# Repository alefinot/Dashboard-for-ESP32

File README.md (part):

# Dashboard++ for ESP32

**Dashboard++** is an ultra-high-performance, production-grade automotive digital instrument cluster and telemetry solution designed for motorcycles, cars, and custom electric/combustion vehicles powered by the **ESP32 WROOM-32** dual-core microcontroller.

Featuring a 4.0-inch ILI9488 TFT display (480×320 resolution) driven over a 60 MHz SPI bus using **LovyanGFX** with PROGMEM-mapped VLW fonts, Dashboard++ blends real-time multi-sensor fusion algorithms, sprite-based anti-aliased digit rendering, dirty-rendering optimizations, hysteresis-based dynamic CPU frequency scaling, persistent NVS configuration management, an Open-Meteo live weather widget, and a complete single-page Web application served over WiFi with REST API control, NVS backup/restore, and firmware updates pushed to it over the LAN.

---

## Technical Table of Contents
1. [Executive Overview](#executive-overview)
2. [System Architecture & Task Allocation](#system-architecture--task-allocation)
3. [Hardware Component Specifications](#hardware-component-specifications)
4. [Hardware Pinout Matrix](#hardware-pinout-matrix)
5. [Software Architecture & Mathematical Models](#software-architecture--mathematical-models)
   - [Dual-Source Speed Fusion & Odometer Engine](#1-dual-source-speed-fusion--odometer-engine)
   - [Anti-Aliased GFX Engine & 7-Segment Fonts](#2-anti-aliased-gfx-engine--7-segment-fonts)
   - [Piecewise Linear Fuel Calibration & Filtering](#3-piecewise-linear-fuel-calibration--filtering)
   - [Steinhart-Hart Coolant Temperature Math](#4-steinhart-hart-coolant-temperature-math)
   - [Fuel Economy & Performance Drag Timer](#5-fuel-economy--performance-drag-timer)
   - [Power Management & Dynamic CPU Scaling](#6-power-management--dynamic-cpu-scaling)
6. [Embedded Web UI & REST API Reference](#embedded-web-ui--rest-api-reference)
7. [NVS Configuration Parameter Reference](#nvs-configuration-parameter-reference)
8. [Android Companion App](#android-companion-app)
   - [The shell: one bar, one pager, one list](#the-shell-one-bar-one-pager-one-list)
   - [The garage: a card is a vehicle and the unit that belongs to it](#the-garage-a-card-is-a-vehicle-and-the-unit-that-belongs-to-it)
   - [Identity: which dashboard belongs to which card](#identity-which-dashboard-belongs-to-which-card)
   - [Connection: where connecting happens, and where it does not](#connection-where-connecting-happens-and-where-it-does-not)
   - [Trip log: one file per power session, tagged with the card](#trip-log-one-file-per-power-session-tagged-with-the-card)
   - [Photos: pick, crop, one JPEG per vehicle](#photos-pick-crop-one-jpeg-per-vehicle)
   - [Building and testing the app](#building-and-testing-the-app)
9. [Codebase Architecture & File Map](#codebase-architecture--file-map)
10. [Build, Installation & Flashing Guide](#build-installation--flashing-guide)
11. [Simulation & Demo Mode](#simulation--demo-mode)
12. [License & Credits](#license--credits)

---

## Executive Overview

Dashboard++ replaces legacy analog or basic digital gauges with an automotive-grade telemetry console. Key capabilities include:

- **Dual Speed Fusion (Hall Effect + GNSS):** Dynamically fuses microsecond-level hardware interrupt pulses with NMEA GPS speed vectors, adjusting confidence based on satellite lock quality ($N_{\text{sat}}$) and cross-checking delta errors.
- **Sprite-Based Anti-Aliased Speed Rendering:** The main speed readout is pre-rendered to an off-screen LGFX_Sprite using a 120px VLW 7-segment digital font, then pushed to the display in a single DMA transfer — reducing SPI bus contention and eliminating per-digit draw calls.
- **PROGMEM VLW Font System:** All fonts (Conthrax SemiBold and DS-DIGIT variants) are compiled into flash as PROGMEM byte arrays (generated from the `.vlw` sources in `data/Fonts/` by `scripts/vlw_to_header.py`), loaded at build time via `loadVLWFont()` — zero DRAM per glyph, no runtime filesystem lookups.
- **Dirty-Rendering Frame Pipeline:** Element state tracking ensures only mutated visual regions are drawn to the SPI bus, with dedicated per-element refresh rate throttles for speed, satellite count, timer, battery, fuel economy, and average speed.
- **Configurable 7-Segment Digital Fonts:** 120px (sprite) and 28px (direct) seven-segment fonts with background "ghost digit" rendering (888 backdrop effect) and fully user-configurable integer and decimal digit boundaries for all telemetry counters.
- **Full Sensor Suite Integration:** Precise fuel level monitoring (20-point piecewise linear calibration table + EMA filtering), engine coolant thermistor telemetry (Steinhart-Hart equation), battery voltage divider monitoring, trip fuel economy tracking, **trip average speed**, and a **session max speed (Vmax)** readout display.
- **FreeRTOS Dual-Core Multitasking:** Strict core isolation — the continuous ~1.1KB/s GNSS UART stream is quarantined in its own Core 0 task (bulk ring-buffer read, bounded per tick, sitting below the WiFi stack), while the vehicle sensor suite and UI rendering run on Core 1, so a GPS stream backlog can never stall the dashboard or freeze any real-time value.
- **Embedded Web Management Portal:** Embedded single-page Web application accessible over SoftAP or local WiFi network featuring grouped card-based configuration UI with live search, real-time performance telemetry panel (FPS, CPU frequency/temp, RAM, flash storage), interactive sliders, color pickers, NVS backup/restore, web serial terminal stream, and OTA firmware updating by uploading a firmware file (from the Web UI file picker, or from the Android app, which is the intended path).
- **Hysteresis-Based Dynamic CPU Scaling:** Three-state frequency governor (240/160/80 MHz) with hysteresis deadbands prevents oscillation, and thermal throttling automatically caps frequency at configurable warning/critical temperature thresholds.

---

## System Architecture & Task Allocation

The system leverages the ESP32's Xtensa dual-core processor via FreeRTOS tasks to guarantee deterministic sensor sampling without visual stuttering or UI delays.

```
┌─────────────────────────────────────────────────────────────────────────────────┐
│                            ESP32 WROOM-32 DUAL-CORE                             │
├────────────────────────────────────────┼────────────────────────────────────────┤
│    CORE 0  (GNSS Stream & Network)     │  CORE 1  (Vehicle Sensors & Display)   │
├────────────────────────────────────────┼────────────────────────────────────────┤
│┌──────────────────────────────────────┐│┌──────────────────────────────────────┐│
││ Task: GpsTaskCore0 (Prio 2, 10KB)    │││ Task: SensorTaskCore1 (Prio 2, 10KB) ││
││                                      │││                                      ││
││• UART2 @ 115200 bulk ring drain      │││• Hall Sensor GPIO33 ISR              ││
││  (readBytes() batch, 1024 B/tick cap)│││• ADC: Fuel (32), Temp (36), Bat (35) ││
││• TinyGPS++ NMEA + UBX NAV-PVT parse  │││• Fuel Economy & Accel Timer          ││
││• Speed Fusion & Odometer calc        │││• Trip Average Speed                  ││
││• GNSS Epoch Time Sync -> settimeofday│││• Safe Thread Sync via g_stateMutex   ││
││• Safe Thread Sync via g_stateMutex   │││                                      ││
││                                      │││• Safe Thread Sync via g_stateMutex   ││
││──────────────────────────────────────│││──────────────────────────────────────││
││ Task: WebTaskCore0 (Prio 1, 12KB)    │││ Main Loop (Priority 1)               ││
││                                      │││                                      ││
││• SoftAP (Dashboard_Config) & STA     │││• Dirty-Rendering Frame Pipeline      ││
││• WebServer HTTP Handlers             │││• LovyanGFX SPI Driver (60 MHz)       ││
││• ArduinoOTA Firmware Listener        │││• Sprite-Based Speed (120px VLW)      ││
││• Serial Log Streaming API            │││• Hysteresis CPU Scaling (80/160/240) ││
│└──────────────────────────────────────┘││• Auto Night-Mode Backlight PWM       ││
│                                        ││• Ignition Deep Sleep State Machine   ││
│                                        ││• Telemetry Logging to 4KB Ring       ││
│                                        │└──────────────────────────────────────┘│
└─────────────────────────────────────────────────────────────────────────────────┘
```

> [!NOTE]
> The GNSS task sits on Core 0 **below** the WiFi/HTTPD/LWIP stack on purpose: the module streams
> ~1.1KB/s continuously and the drain is I/O-gated at the byte arrival rate, so it can never
> out-run the stream. GPS is 1Hz-tolerant data, so if the network preempts the drain, only GPS
> values lag — the vehicle sensors and the screen are never touched.

> [!NOTE]
> The **weather fetch task** (Core 0, spawned by `startWeatherFetch()` on Core 1) polls the Open-Meteo
> API on a configurable interval (`WEATHER_REFRESH_MIN`) and stores the result in a dedicated
> `g_weatherData` struct. A 30 s guard asks a stuck fetch to abort (the fetch polls
> `weatherAbort` at its checkpoints and HTTP calls carry 8 s connect/read timeouts) so it unwinds
> and deletes itself rather than being killed with `vTaskDelete()`; while an aborted fetch is still
> alive, `startWeatherFetch()` refuses to stack a second one. A config save triggers an
> instant refetch with a 2 s retry backoff.

> [!NOTE]
> Every FreeRTOS task is started through `startTask()` in `src/main.cpp`, which checks the
> `xTaskCreatePinnedToCore()` return value, retries once on half the requested stack (a reduced
> stack usually fits and beats a missing subsystem) and, if that fails too, records the task in a
> `failedTasksMask` and logs it with the free heap. A task that cannot start is therefore named in
> the boot log instead of silently missing — the failure that used to show up only as a frozen
> heartbeat, no Web UI or dead sensors.

---

## Hardware Component Specifications

| Component | Part / Model | Protocol / Signal | Specifications |
| :--- | :--- | :--- | :--- |
| **Microcontroller** | ESP32-WROOM-32 | Xtensa 32-bit LX6 | Dual-core 240 MHz, 520 KB SRAM, 4 MB SPI Flash, RTC IO |
| **Display Panel** | ILI9488 TFT LCD (4.0") | SPI3 (16-bit RGB565) — SCLK GPIO18, MOSI GPIO23, CS GPIO5, DC GPIO27, RST GPIO14 (no MISO) | 480×320 pixels, 60 MHz SPI bus speed (clamped to 1–80 MHz), hardware CS/DC/RST |
| **Display Backlight** | LED Backlight (`BL_DISPLAY`, GPIO12) | LEDC PWM — pin-based `ledcAttach(BL_DISPLAY, BL_PWM_HZ, 8)` | hardware PWM at `BL_PWM_HZ` (default **12 kHz** — above the audible range — configurable 1–40 kHz), 8-bit resolution (256 brightness levels), logarithmic fading; the LEDC channel is assigned by the arduino-esp32 3.x wrapper |
| **GNSS Module** | BZGNSS P25 Pro (u-blox M10) | UART2 (RX=GPIO16, TX=GPIO17) | 115200 baud (configurable), UBX NAV-PVT / NMEA 0183 stream (module is preconfigured — the firmware is receive-only), 10 Hz update rate, multi-constellation (GPS/GLONASS/BDS/Galileo), UTC epoch time synchronization |
| **Wheel Speed Sensor** | Hall Effect Interrupt | GPIO33 (Input Pullup) | Any-edge ISR stamps the edges; interval/filter logic runs on the sensor task, microsecond timing |
| **Fuel Level Sensor** | Marine Resistive Sender (capacitive touch removed in v1.3.6) | GPIO32 (ADC1_CH4) | Voltage divider behind an excitation resistor, ohm-domain calibration table (up to 20 points), oversampling + EMA smoothing, open/short detection |
| **Engine Temp Sensor** | NTC Thermistor (10k/100k) | GPIO36 (ADC1_CH0) | Analog 0–3.3V, Steinhart-Hart equation, voltage divider balance |
| **Battery Voltage** | Voltage Divider (5.7:1) | GPIO35 (ADC1_CH7) | Analog 0–3.3V, range 0–18.8V DC, sampled every 500 ms |
| **Power / Ignition** | Ignition Key Sense Line | GPIO4 | High=Ignition ON, Low=Power Lost → Animated Deep Sleep |

---

## Hardware Pinout Matrix

> For the board side of the same information — which connector/plug each signal lives on,
> with the connector pin numbers and the small-part roles — see
> [`hardware/PINOUT.md`](hardware/PINOUT.md).

| ESP32 Pin | Function Name | Peripheral Type | Signal Direction | Hardware Configuration & Notes |
| :---: | :--- | :--- | :---: | :--- |
| **GPIO0** | BOOT | Factory Reset | Input (Pullup) | `pinMode(0, INPUT_PULLUP)`; **hold BOOT 4 s, release, hold 4 s again** within the first 30 s after boot to wipe the config — the reliable path. The release in the middle is required because GPIO0 is shared with the serial adapter's DTR line through the auto-reset transistor: a PC that holds DTR asserted keeps GPIO0 low forever, and the old single 8 s hold wiped the config on every boot with nobody touching the board. The serial fallback (send `RESET` within the first 2 s of boot) is matched against a rolling 32-character window, so boot-log echo can no longer fill the capture and hide the command (issue #39) |
| **GPIO1** | Console TX | Debug Console | Output | `Serial.setPins(1, 3)` pins the console explicitly (arduino-esp32 3.x moved the UART1 default to GPIO26/27) |
| **GPIO3** | Console RX | Debug Console | Input | Same `Serial.setPins(1, 3)` call |
| **GPIO4** | `POWER_SENSE_PIN` | Power Sense | Input (No Pull) | Ignition sense line; triggers EXT0 RTC wake up from deep sleep |
| **GPIO5** | `CS_DISPLAY` | SPI Chip Select | Output | Hardware SPI CS for ILI9488 Display |
| **GPIO12** | `BL_DISPLAY` | Backlight PWM | Output | Pin-based `ledcAttach(BL_DISPLAY, BL_PWM_HZ, 8)` — frequency is the `BL_PWM_HZ` knob (default 12 kHz, above hearing), 8-bit resolution |
| **GPIO14** | `SPI_RST` | Display Reset | Output | Active-Low hardware reset line for ILI9488 |
| **GPIO16** | `GNSS_UART2_RX_PIN` | GPS Serial RX (UART2) | Input | Connected to the GNSS module TX pin. Receive-only: the firmware never transmits to the module |
| **GPIO17** | `GNSS_UART2_TX_PIN` | GPS Serial TX (UART2) | Output | Connected to the GNSS module RX pin; configured but idle - no UBX command is ever sent |
| **GPIO18** | `cfg.pin_sclk` | SPI Clock | Output | Hardcoded in `gfx.cpp` (SPI3_HOST), 60 MHz default |
| **GPIO23** | `cfg.pin_mosi` | SPI Master Out | Output | Hardcoded in `gfx.cpp`, LCD data/command stream |
| **GPIO25** | `TRIP_RESET_PIN` | Trip Reset Button | Input (Pullup) | Momentary push button to GND; hold `TRIP_RESET_HOLD_MS` to zero the trip stats (issue #17). Internal ~45 kΩ pull-up, no external parts |
| **GPIO27** | `SPI_DC` | Data / Command | Output | High = Data, Low = Command for ILI9488 controller |
| **GPIO32** | `FUEL_TOUCH_PIN` | Fuel sender input | Input | Dedicated ADC1 Channel 4 pin: 3V3 → `FUEL_EXC_RES_OHM` → GPIO32 → sender → tank ground (capacitive touch removed in v1.3.6) |
| **GPIO33** | `HALL_SENSOR_PIN` | Hall Interrupt | Input (Pullup) | Any-edge (`CHANGE`) hardware interrupt: the ISR timestamps both transitions, the filter chain validates them on the sensor task |
| **GPIO34** | `LIGHT_SENSOR_PIN` | Ambient Light | Input (No Pull) | LDR ambient light sensor for auto-brightness (calibrated via `/api/ambient/cal-dark` / `cal-bright`) |
| **GPIO35** | `BATTERY_SENSE_PIN` | Battery ADC | Input (No Pull) | Connected to 5.7:1 precision resistor divider node |
| **GPIO36** | `TEMP_SENSE_PIN` | Engine Temp ADC | Input (No Pull) | Connected to NTC thermistor / balance resistor divider node |

> [!IMPORTANT]
> GPIO32 is dedicated to the fuel ADC input to avoid pin-sharing conflicts with the GPIO33 Hall interrupt hardware line.

> [!NOTE]
> This matrix matches the code (`src/dashboard.h` pin defines and the hardcoded display SPI pins in `src/gfx.cpp`), which is the source of truth. The GNSS serial pair moved from GPIO25/26 to **GPIO16/17** during the pin-swap test and stayed there, which is what freed **GPIO25** for the trip-reset button; **GPIO26** stays free as the spare for a second button. Strapping pins (`GPIO0`, `GPIO2`, `GPIO5` = `CS_DISPLAY`, MTDI/`GPIO12`, MTDO/`GPIO15`) are deliberately not used for buttons — a button to GND can hold them the wrong way during reset and block boot. The display SPI bus has no MISO line (`cfg.pin_miso = -1`), and GPIO21/22 (former compass I²C) are unused.

---

## Software Architecture & Mathematical Models

### 1. Dual-Source Speed Fusion & Odometer Engine

Dashboard++ features a dual-source speed calculation engine that combines low-latency wheel rotation timing with absolute satellite GPS telemetry.

#### Hall Sensor Calculation & 5-Layer Defense Pipeline
Speed is derived from microsecond timing between consecutive interrupt pulses on GPIO33, protected by an end-to-end 5-layer defense pipeline that eliminates spark ignition EMI glitches, prevents baseline collapse during deceleration, and bounds rate-of-change to physical limits:

1. **Layer 1: Measured Pulse-Width Qualification (Glitch Filter):** Real wheel magnets hold GPIO33 LOW for hundreds of microseconds (one revolution at 200 km/h is still 29.7 ms long). High-frequency ignition coil ringing collapses back to HIGH within <10 µs. The GPIO ISR used to prove the width by busy-waiting `HALL_PULSE_MIN_US` and re-sampling `REG_READ(GPIO_IN1_REG)` **inside** the interrupt, which masked interrupts on that core for up to 1 ms per glitch (~86 bytes of GNSS RX at 115200 baud). Now the interrupt is `CHANGE` (both edges), the ISR only stamps the transition time into a 64-slot ring, and the qualification is *measured*: `rise − fall ≥ HALL_PULSE_MIN_US` (default 150 µs, WebUI-tunable, clamped to 10…1000 µs). A glitch is dropped before any interval logic runs, exactly as before, and the ISR stays at roughly a microsecond. Ring overflow drops the newest edge and is counted as `drop=` in the `HALL:` telemetry line; the accept latency is reported as `lag=`.
2. **Layer 2: Anti-Collapse Timing Baseline (Integer Guard) + Period Guard:** 100% integer timestamping and period guard with zero floating-point math, in the validation step that runs on the sensor task (`processHallEdges()`). When actively rolling, candidate intervals faster than $2\times$ previous speed ($gap \times 2 < last$) are dropped without updating `lastHallPulseTimeUs` or the stable baseline `hallStableIntervalUs`. This prevents spark bursts during braking from collapsing the guard baseline and producing >200 km/h spikes. The complementary upper bound is `HALL_PERIOD_GUARD`: an interval more than $N\times$ the last accepted one is dropped too (a wheel cannot slow $N$-fold in a single revolution; a genuine stop is handled by Layer 3 instead). $N = 1$ disables it.
3. **Layer 3: Standstill Detection, Buffer Purge & Deceleration Decay:** If time since the last pulse exceeds `STANDSTILL_TIMEOUT_US` (1.5 s), the wheel was stopped. The first pulse synchronizes the timing baseline, holds its odometer credit until a confirming pulse follows, and completely purges the history ring buffer. During deceleration, if elapsed time $dt$ since the last pulse exceeds $1.5\times$ the rotation period (plus the recorded accept latency `lag`, so deferred validation cannot make an on-time pulse look overdue), dynamic decay constrains speed smoothly to 0 km/h without mid-revolution diving.
   - **Layer 3b: Confirmed-Roll Speed Gate:** the purge in Layer 3 also disarms Layer 2 (which is conditioned on the rolling state) and leaves the median window with a single sample, so before this gate *one* accepted inter-edge gap became the displayed speed — two ignition-EMI edges 12 ms…1.5 s apart on a parked machine reported a plausible reading (100 ms → 59 km/h on a 1650 mm wheel). The speed output now stays at 0 until `HALL_CONFIRM_REVS` (3) consecutive accepted intervals agree pairwise within $2\times$ — the same physical bound Layer 2 uses while rolling. Cost: a genuine roll start is displayed two revolutions later (≈0.6 s at 12 km/h, ≈0.2 s at 30 km/h). Distance credits are unaffected (the odometer is guarded by the pending-anchor logic). Below ~4 km/h the 1.5 s standstill timeout already reports 0, so the usable low-speed floor does not change.
4. **Layer 4: Physical Slew-Rate Limiter (Max Accel / Decel):** Terrestrial motorcycles cannot exceed physical acceleration limits (~1.7g / 60 km/h/s) or emergency braking (~2.3g / 80 km/h/s). Clamping $\Delta V$ between update ticks (~20 ms) mathematically prevents instantaneous multi-hundred km/h jumps on the speedometer.
5. **Layer 5: Sensor Fusion Outlier Rejection:** In Sensor Fusion mode (2), if Hall speed reads $> V_{\text{gps}} + 30\text{ km/h}$ while GPS has a solid satellite lock, the Hall reading is rejected as an anomalous spike and the dashboard displays GPS speed.

#### Speed Source & Fusion Logic
The displayed speed source is selected by `SPEED_SOURCE_MODE`: `0`=Hall only, `1`=GPS only, `2`=Sensor Fusion (default).

In **Sensor Fusion mode (2)**, the engine dynamically balances both sensors:
- **Rock-Solid Standstill:** When $V_{\text{hall}} = 0$ and $V_{\text{gps}} < \text{GPS\_START\_KMH}$ (3.0 km/h), speed is forced to solid `0.0 km/h`, eliminating GPS drift at traffic lights.
- **Immediate Response:** As soon as wheel pulses arrive ($V_{\text{hall}} > 0$), speed is displayed immediately without clamping.
- **Dynamic Throttle Tracking:** When $|V_{\text{gps}} - V_{\text{hall}}| > \text{MAX\_SPEED\_DELTA\_KMH}$ (such as normal GPS lag during rapid acceleration), Hall is trusted directly so throttle response is never suppressed.
- **Dual Failsafe Redundancy:** If the Hall sensor fails or disconnects at speed, the system automatically falls back to valid GPS ($V_{\text{gps}} \ge 3.0\text{ km/h}$). If GPS signal is lost in a tunnel, Hall sensor carries 100% of the speed. Speed never drops to 0 while moving.
- **Dynamic Confidence Blending:** When both sensors are healthy and consistent ($\Delta V \le \text{MAX\_SPEED\_DELTA\_KMH}$):
$$C_{\text{sat}} = \text{constrain}\left(\frac{N_{\text{sat}} - N_{\text{min}} + 1}{N_{\text{opt}} - N_{\text{min}} + 1}, 0.0, 1.0\right)$$
$$C_{\delta} = \text{constrain}\left(1.0 - \frac{\Delta V - \Delta V_{\text{min}}}{\Delta V_{\text{max}} - \Delta V_{\text{min}}}, 0.0, 1.0\right)$$
$$W_{\text{gps}} = C_{\text{sat}} \cdot C_{\delta} \cdot 0.5$$
$$V_{\text{fused}} = (W_{\text{gps}} \cdot V_{\text{gps}}) + ((1 - W_{\text{gps}}) \cdot V_{\text{hall}})$$
Capping $W_{\text{gps}}$ at 0.5 ensures Hall sensor's zero-latency dynamic throttle/brake response is always preserved, while GPS anchors long-term tire wear accuracy.

#### Odometer Persistence Strategy
To protect the ESP32 NVS Flash memory from wear, distance accumulation runs continuously in RAM. The odometer writes to non-volatile storage **only after accumulating a full 1.0 km increment**:
$$\Delta D_{\text{ram}} \ge 1.0\text{ km} \implies \text{Preferences.putDouble("odo", } D_{\text{total}}\text{)}$$

**Sharing the odometer across cores.** The odometer is a 64-bit `double`, and a 64-bit load/store on ESP32 is two 32-bit bus cycles: a read that lands between the two halves of a write returns a mixture of two different distances. The totals therefore live file-local in `src/sensors.cpp` and every other task reaches them through the locked accessors `odoGet()`, `odoSet()`, `odoAdd()` (read-modify-write in one critical section), `odoLastSaved()` and `odoMarkSaved()`, guarded by a dedicated spinlock (`odoMux`) — deliberately *not* `g_stateMutex`, so the display never waits behind sensor or NVS work and the critical sections stay a few instructions long. The accessors never write flash; the 1 km wear discipline above is unchanged.

#### UBX Frame Parser (receive-only)

The module streams UBX and NMEA on the same UART, so `src/sensors.cpp` runs a byte-at-a-time state machine (`ubxParseByte`) alongside TinyGPS++: it locks onto `0xB5 0x62`, reads class/id/length, seeds both Fletcher-8 accumulators by stepping through each header byte individually, and hands a checksum-valid NAV-PVT to the NMEA side. It never transmits anything (see the receive-only rule).

- **Length is honoured, including zero.** A zero-length payload goes straight to the checksum states — entering the payload state with `len = 0` used to consume `CK_A`/`CK_B` as payload, corrupt the accumulators and raise a spurious `CKFAIL`, leaving the parser to resync by luck on the next `0xB5` (issue #33).
- **Oversize frames are dropped at the header** (`len > 92`) rather than overflowing the payload buffer, and a bad checksum drops exactly one frame before resyncing.
- **Counters, not silence:** `ubxSyncSeen`, `ubxCkFail`, `ubxOversize` are reported in the GPS debug telemetry so a framing problem is visible instead of looking like lost satellites.
- **Checked offline:** `python scripts/verify_ubx_parser.py` runs a host replica of the state machine against hand-built frames — NAV-PVT (92 B), ACK (10 B), zero-length, poisoned checksum, garbage/false-sync, oversize, back-to-back frames — and asserts that the old zero-length path still fails, so the regression cannot come back unnoticed.

---

### 2. Anti-Aliased GFX Engine & 7-Segment Fonts

Graphics rendering is built on `LovyanGFX` with specialized antialiasing routines and a PROGMEM-mapped VLW font system (compiled into flash — no runtime filesystem lookups, zero DRAM per glyph).

#### Text Bounds Contract (`getTextBounds`)

`LGFX_ST7789_4::getTextBounds()` (declared in `src/dashboard.h`, defined in `src/gfx.cpp`) reports **advance-based** bounds, not ink bounds: `w` is `textWidth()` (the advance the string consumes), `h` is the font line height, `y1` is `-baseline`, and **`x1` is always `0` by contract** (issue #44). Every layout path — 7-segment digit cells, the weather/accel badges, the centred splash and signature strings — places text on advances, and the `- x1` terms those expressions carry are the documented slot where a real per-glyph left bearing would flow through, not a live correction. Code must not treat `x1` as a measured bearing; if ink bounds are ever needed, a separate helper gets added rather than these semantics changing. The `digitXOff[]` / `ds15_digitXOff[]` tables fed from it are therefore advance-only offsets by construction.

#### Alpha Blending Math
Sub-pixel anti-aliased primitives draw edges with fractional coverage $\alpha \in [0, 1]$. Color blending uses fast integer arithmetic:
$$R_{\text{out}} = \lfloor (R_{\text{bg}} \cdot (256 - a) + R_{\text{fg}} \cdot a) \gg 8 \rfloor$$
$$G_{\text{out}} = \lfloor (G_{\text{bg}} \cdot (256 - a) + G_{\text{fg}} \cdot a) \gg 8 \rfloor$$
$$B_{\text{out}} = \lfloor (B_{\text{bg}} \cdot (256 - a) + B_{\text{fg}} \cdot a) \gg 8 \rfloor$$

#### Sprite-Based Speed Rendering
The main speed display is rendered to an off-screen `LGFX_Sprite` using the VLW 120px 7-segment digital font. Ghost digits (888 backdrop) and active digits are drawn once per frame into the sprite, then pushed to the display in a single DMA transfer — drastically reducing SPI bus transactions compared to per-digit draw calls.

#### VLW Font System
All typography is compiled into flash as PROGMEM byte arrays (`include/*.h`, generated from the `.vlw` sources in `data/Fonts/` by `scripts/vlw_to_header.py`):
- `DS-DIGIT_120px.vlw` → `DS_DIGIT_120px_vlw.h` — Main speed readout (sprite-rendered)
- `DS-DIGIT_28px.vlw` → `DS_DIGIT_28px_vlw.h` — Secondary digits (time, odometer, satellite, battery, fuel economy, average speed)
- `Conthrax_SemiBold_28px.vlw` → `Conthrax_SemiBold_28px_vlw.h` — Section headers and badges
- `Conthrax_SemiBold_16px.vlw` → `Conthrax_SemiBold_16px_vlw.h` — Unit labels and sidebar text
- `Conthrax_SemiBold_10px.vlw` → `Conthrax_SemiBold_10px_vlw.h` — Micro labels (AVG badge, IST badge)

Legacy compiled-in GFX font bitmaps (`Conthrax_SemiBold4pt7b`, `Conthrax_SemiBold7pt7b`) are retained as fallbacks for the badge/label sizes.

---

### 3. Marine Resistive Fuel Sender: Divider, Ohm-Domain Table & Filtering

Fuel level is read from a standard marine resistive sender wired as a voltage
divider on `FUEL_TOUCH_PIN` (GPIO32). The capacitive pad this input used to carry
is gone; the pin is now a plain ADC input (issue #18):

```
3V3 ─── FUEL_EXC_RES_OHM ─── GPIO32 (ADC1_CH4) ─── sender ─── tank ground
```

#### From ADC code to ohms
`FUEL_OVERSAMPLE` conversions are averaged into a raw code $\bar{S}$ (software
oversampling — the core exposes no hardware averaging for this pin), turned into
a voltage with `FUEL_ADC_VREF` (the 3.3 V rail — since issue #55 it is not a Web
UI field any more), and the sender resistance is recovered from the divider:

$$V = V_{\text{ref}} \cdot \frac{R_{\text{sender}}}{R_{\text{sender}} + R_{\text{exc}}} \qquad\Rightarrow\qquad R_{\text{sender}} = R_{\text{exc}} \cdot \frac{V}{V_{\text{ref}} - V}$$

The calibration table (`fuelCalOhms`) stores **ohms, not ADC codes**. That is
what makes any sender standard work on the same firmware — SAE **10–180 Ω**
(low = empty), European/VDO **240–33 Ω** (high = empty), GM **0–90 Ω** — and it
means a captured table still means the same thing after the excitation resistor
(or the sender) is swapped. `FUEL_OHM_EMPTY` / `FUEL_OHM_FULL` describe the
sender: they size the exciter, define the fault band, and pre-fill the table
ramp; they do not replace the table.

#### EMA + piecewise interpolation
Smoothing stays in the ADC-code domain (linear, and the same domain the table was
captured against), then the ohm value walks the table:
$$\bar{S}_t = (\alpha \cdot S_t) + ((1 - \alpha) \cdot \bar{S}_{t-1}) \qquad \alpha = \texttt{FUEL\_FILTER\_ALPHA}\ (default{=}0.08)$$
Given $N$ table points $T[0 \dots N-1]$ mapped to tank slots $0 \dots N-1$, find
segment $i$ containing $R_{\text{sender}}$:
$$L_{\text{fuel}} = i + \left(\frac{R_{\text{sender}} - T[i]}{T[i+1] - T[i]}\right)$$
$$\text{FuelPercentage} = \text{constrain}\left(\left\lfloor \frac{L_{\text{fuel}}}{N - 1} \times 100 \right\rfloor, 0, 100\right)$$

The traversal direction is taken from the table's two ends, so a rising (SAE) and
a falling (European) sender are both handled without a mode switch.

#### Sender fault detection
The failure that makes a self-built sender useless is an open line that still
looks like a plausible reading, so the input is classified every sample and shown
in the Web UI instead of being turned into a tank level:

| Condition | Reported as |
| :--- | :--- |
| `FUEL_INPUT_ENABLED` off | **no input** — gauge pinned at 0, a floating pin never invents a level |
| pin within 0.5 % of the rail, or $R > 3 \times$ the entered full/empty maximum | **open circuit** — sender unplugged, wire broken, arm off the pivot |
| $R$ below `min(EMPTY, FULL)` by more than `max(5 Ω, 25 %)` | **shorted input** — signal wire on ground |

Demo mode drives the same pipeline: the simulated level is converted back through
the calibration table into a divider code and read forward again, so the table,
divider math and fault band are exercised with no hardware fitted (rule 20).

#### Excitation resistor sizing
$R_{\text{exc}}$ is a trade: the geometric mean of the sender range spreads the
span over the most volts, but pushes more current through the sender element. The
Web UI suggests the best E12 value for the entered range under a **15 mA** sender
current budget and keeps the top of the span below 2.6 V, because a reading
pinned near the rail is indistinguishable from an open circuit. For the shipped
10–180 Ω default that suggestion is 220 Ω — the same value the firmware ships
with — giving a 1.34 V span at 14.3 mA.

Check the whole chain on a host with `python scripts/verify_fuel_ohms.py`
(divider round-trip, both conventions, resolution per tank slot, demo round-trip,
fault band, exciter suggestion).

---

### 4. Steinhart-Hart Coolant Temperature Math

Engine temperature is measured via an NTC thermistor connected in a resistor divider configuration with a balance resistor $R_{\text{balance}}$ (default=10,000 $\Omega$).

#### Voltage Divider Resistance Calculation
$$V_{\text{out}} = \text{ADC}_{\text{raw}} \times \left(\frac{3.3}{4095}\right)$$
$$R_{\text{ntc}} = R_{\text{balance}} \times \left(\frac{V_{\text{out}}}{3.3 - V_{\text{out}}}\right)$$

#### Steinhart-Hart B-Parameter Equation
$$T_{\text{Kelvin}} = \left( \frac{1}{\beta} \cdot \ln\left(\frac{R_{\text{ntc}}}{R_{\text{room}}}\right) + \frac{1}{T_{\text{room}}} \right)^{-1}$$
$$T_{\text{Celsius}} = T_{\text{Kelvin}} - 273.15$$
where $R_{\text{room}} =$ `NTC_R25` (default=10,000 $\Omega$), $T_{\text{room}} = 298.15\text{ K}$ ($25^\circ\text{C}$), and $\beta =$ `NTC_BETA` (default=3950). A fixed `NTC_TEMP_OFFSET` (°C, default=0.0) is added to the result to correct a systematic reading bias.

#### WebUI Sensor Calibration
The **Sensors Tuning** WebUI card calibrates the two analog sensors against a reference, using the live `/api/live` snapshot the page polls once per second (no raw-ADC conversion needed):
- **Fuel level Sensor** — the live sender resistance (Ω) is shown next to a fault state (`open` / `shorted` / `out of range` / `no sender`). Two ways to build the table (`fuelCalOhms`): **Fill from empty/full ohm** pre-fills a linear ramp from `FUEL_OHM_EMPTY` to `FUEL_OHM_FULL` (a good start, no driving needed), or drive the tank through its levels and **Capture** the live reading into each slot — slot `0` = empty, slot `N-1` = full. Changing the point count regenerates the ramp. The card is titled without the pin number (issue #55), and the excitation-resistor suggestion is computed from the empty/full ohms on the page plus the fixed 3.3 V rail.
- **Speedometer** — `SPEED_SOURCE_MODE`, `SPEED_SOURCE_HOLD_MS`, the two hall-vs-GPS deviation bands (`GPS_MIN_DEV_KMH`, `MAX_SPEED_DELTA_KMH`), the GPS start/stop pair (`GPS_START_KMH`, `GPS_STOP_SETTLE_MS`) and the wheel-signal filters (`HALL_MEDIAN_SAMPLES`, `HALL_PERIOD_GUARD`, `HALL_PULSE_MIN_US`), in that order (issue #56). The GNSS hardware rows (baud, satellite counts) stay in the GPS block.
- **Engine Temperature** — the live reading is shown; type a reference temperature and press **Apply** to set `NTC_TEMP_OFFSET`. `NTC_R25`, `NTC_R_BALANCE` and `NTC_BETA` are under **Advanced**.
- **Battery Voltage** — the live reading is shown; type a reference voltage (e.g. a multimeter) and press **Apply** to set `BATTERY_OFFSET`. `BATTERY_SCALE` (divider ratio) is under **Advanced**.
- Calibrating against a live reading means no raw-ADC arithmetic in the browser: the offset is derived on the device from the value it is currently seeing.

---

### 5. Fuel Economy & Performance Drag Timer

#### Instantaneous & Trip Fuel Economy
- **Trip Average (KM/L):** $KM/L_{\text{avg}} = \frac{D_{\text{trip}}}{C_{\text{consumed}}}$. The trip is zeroed only by an explicit trip reset — the physical button on GPIO25, `POST /api/trip/reset`, or a factory reset — never by a detected refuel (issue #17). A fuel-level rise still re-anchors the consumption baseline so the average stays sane, but it leaves the trip distance and the averages alone.
- **Instantaneous (KM/L):** Calculated across a 3-second sliding window:
  $$KM/L_{\text{inst}} = 0.4 \cdot \left(\frac{\Delta D_{3\text{s}}}{\Delta C_{3\text{s}}}\right) + 0.6 \cdot KM/L_{\text{inst, prev}}$$
- **Trip Average Speed (KM/H):** $V_{\text{avg}} = \frac{D_{\text{trip}}}{t_{\text{elapsed}}}$, displayed in the bottom row alongside fuel economy readouts.
- **Session Max Speed (Vmax):** The highest fused/filtered speed reached this power-on session; held on screen until the next reboot (RAM-only, no NVS persistence, no manual reset). Rendered as the **MAX** icon in the bottom row — same 28px 7-segment structure as the Instant KM/L readout — in MPH under imperial. Controlled by `SHOW_ELEMENT_MAX_SPEED`, `OFFSET_MAX_SPEED_X/Y`, `ALIGN_MAX_SPEED`, `MAX_SPEED_INT_DIGITS`, `MAX_SPEED_DEC_DIGITS`, and the `REFRESH_MAX_SPEED_MS` redraw throttle.

#### Acceleration Performance Timer
Measures time taken to accelerate between configured speed thresholds (`ACCEL_START_SPEED` to `ACCEL_TARGET_SPEED`, e.g., 0–50 km/h or 0–100 km/h) using a 3-state state machine with configurable timeout (`ACCEL_MAX_TIME`, default=30s):

```
  ┌─────────┐    Speed >= StartSpeed     ┌─────────┐
  │  READY  │ ─────────────────────────> │ RUNNING │
  └─────────┘                            └─────────┘
       ▲                                      │
       │ Speed < Start (Reset)                │ Speed >= TargetSpeed OR Timeout
       └──────────────────────────────────────┼───────────────────────┐
                                               ▼                       │
                                         ┌──────────┐                  │
                                         │ FINISHED │ <────────────────┘
                                         └──────────┘
```

---

### 6. Power Management & Dynamic CPU Scaling

To balance processing performance, power consumption, and thermal stability, Dashboard++ includes dynamic CPU management and ignition sensing.

#### Hysteresis Dynamic Scaling Matrix

The governor uses a 3-state machine with hysteresis deadbands to prevent frequency oscillation:

```
                      ┌──────────────────────────────┐
                      │ Read Current Measured FPS &  │
                      │ Die Temp (temperatureRead()) │
                      └──────────────┬───────────────┘
                                     │
                     Is ENABLE_DYNAMIC_CPU true?
                     ├─── NO  ──> Set MANUAL_CPU_FREQ (80 / 160 / 240 MHz)
                     └─── YES ──> Check current state:
                                    ├── State = 240 MHz:
                                    │    └── FPS > 85% Target → 160 MHz
                                    │    └── else → stay at 240 MHz
                                    ├── State = 160 MHz:
                                    │    ├── FPS < 65% Target → 240 MHz
                                    │    ├── FPS > 95% Target → 80 MHz
                                    │    └── else → stay at 160 MHz
                                    └── State = 80 MHz:
                                         ├── FPS < 45% Target → 240 MHz
                                         ├── FPS < 70% Target → 160 MHz
                                         └── else → stay at 80 MHz
                                    │
                                    └── Apply Thermal Throttling:
                                          ├── Temp >= CRIT (70°C): Force 80 MHz
                                          └── Temp >= WARN (60°C): Cap at 160 MHz
```

#### Ignition Loss & Deep Sleep Transition
When `ENABLE_POWER_SENSE` is enabled and `POWER_SENSE_PIN` (GPIO4) stays **continuously LOW for `POWER_SENSE_OFF_MS`** (default 10 s, 500–120000 ms):
1. Plays goodbye screen animation (`showGoodbyeScreen(true)`).
2. Fades display backlight down to 0% via LEDC PWM.
3. Configures RTC EXT0 wake-up trigger on GPIO4 (High level).
4. Invokes `esp_deep_sleep_start()`.

The line is debounced in software (`powerSenseOffConfirmed()` in `src/sensors.cpp`): the timer restarts on every HIGH, so ignition bounce, a load-dump dip or a flaky ground of a few milliseconds up to several seconds cannot stall the GPS/odometer task or put the unit to sleep (issue #26). A single LOW sample used to be enough. Side effect: key-off costs `POWER_SENSE_OFF_MS` of live current draw before the goodbye screen and sleep; wake behaviour is unchanged (EXT0 on GPIO4 going HIGH).

---

## Embedded Web UI & REST API Reference

Dashboard++ embeds a single-page management portal directly into flash memory (`index_html`).

### WiFi Network Connectivity
- **SoftAP Mode:** Emits AP SSID `Dashboard_Config` (Default IP: `192.168.4.1`). Always up alongside the client connection (`WIFI_AP_STA`), secured by `AP_PASSWORD` (empty or 8–63 characters).
- **Multi-SSID Client Mode:** Stores up to 5 networks. They are tried in slot order, and the search **never expires** — a failed cycle is simply followed by another one, forever (there is no search-policy parameter to set). The order is **automatic**: when a network joins, it is moved to slot 0, so the network this unit actually reached last is the first one tried after a reboot or a dropout — no hand-ordered “primary / fallback 1…4”. Credentials are only ever removed by an explicit **Forget**; being out of range is the normal state for a vehicle and never deletes a network by itself.
- **Phone-style network picker (Web UI → Network → Wifi):** press **Scan Networks**, tap the network, type the passphrase once. Open networks join without a password, a network that is already stored reconnects without asking for it again, and a hidden network is added by name. The scan is a cached list of the 30 strongest SSIDs (channels 1–13); it is never refreshed automatically, because a scan moves the radio off its working channel — it runs when asked and after a failed search cycle. With all five slots full the device refuses to guess: the UI asks which stored network may be replaced.

> [!IMPORTANT]
> **Access model (deliberate).** The config portal and the REST API have **no login** — access control is the Wi-Fi itself. `AP_PASSWORD` must be empty or 8–63 characters; a shorter value is rejected and the default (`12345678`) is restored, so the hotspot can never come up with a password the ESP32 silently refused. **Change that default before using the dashboard on a public network**: anyone who joins the hotspot (or reaches the dashboard's LAN IP) can change settings and flash firmware.

### Web UI Features
The management portal features a modern grouped card-based layout:
- **Collapsible sections** with smooth accordion animations (non-JS fallback)
- **Live search bar** to filter configuration parameters across all sections
- **Autosave** triggered 2 seconds after any input change
- **Visible checkboxes** (UI Layout → Screen Elements) control only what is drawn on the display; sensors, GPS, odometer and every calculation keep running whether the element is visible or not, so hiding a readout never stops the data behind it
- **Advanced Mode** switch in the header reveals the technical parameters, so the common setup path stays short (see `ADV_MODE`)
- **Color pickers** with inline preview for all UI color values
- **Slider + number inputs** with mouse-wheel scroll protection for all range parameters
- **XY offset controls** with linked sliders for UI element positioning
- **Real-time performance panel** displaying FPS, CPU frequency/temperature, RAM usage, flash storage utilization, and live serial output monitor
- **Weather Widget group** with city, latitude/longitude, refresh interval, locale, and a day/night icon
- **Ambient light calibration** (dark / bright reference points)
- **OTA firmware upload** via file picker (the Web UI path; the Android app pushes the same way and additionally lists the published releases so a person picks which one to install)
- **NVS backup/restore** (export downloads `GET /api/config` as `dashboard_backup.json`, import posts it back to `POST /api/config`)

### REST API Endpoints

| Endpoint | Method | Description | Request Payload / Params | Content-Type |
| :--- | :---: | :--- | :--- | :--- |
| `/` | `GET` | Serves pre-gzipped single-page Web UI | None | `text/html` |
| `/debug` | `GET` | Dump first bytes of the pre-gzipped UI buffer (build sanity check) | None | `text/plain` |
| `/api/config` | `GET` | Exports complete NVS configuration plus read-only `build_version` | None | `application/json` |
| `/api/config` | `POST` | Updates NVS parameters and applies changes; on a save where N values could not be written the answer carries `nvsErrors: N`, `nvsFailedKeys: "KEY,…"` and `nvsAvailable` (free NVS entries) | Config JSON object | `application/json` |
| `/api/wifi/scan` | `GET` | Cached Wi-Fi scan plus the stored networks: `scanning`, `ageMs`, `count`, `max: 30`, `nets[]` (`ssid`, `rssi`, `ch`, `auth`, `authName`, `saved`) and `saved[]` (`slot`, `ssid`, `connected`). Reading it never touches the radio | None | `application/json` |
| `/api/wifi/scan` | `POST` | Queues a background scan of channels 1–13 (the radio leaves its channel for a few seconds, which is why the firmware never scans on its own); poll `GET` for the result | None | `application/json` (`{"status":"requested"}` / `{"status":"scanning"}`) |
| `/api/wifi/join` | `POST` | Stores one network and searches for it immediately. An SSID already stored keeps its slot (with no `pass` field the stored passphrase is reused, not blanked); otherwise the first free slot is used. With all five taken the answer is `status:"full"` plus the stored list, and re-sending with `"slot":n` names the network to displace | `{"ssid":"…","pass":"…"}` — `pass` omitted = reuse stored / open network; `"slot":n` = overwrite that slot | `application/json` (`status`, `slot`, `ssid`, `nvsOk`, `overwrite`) |
| `/api/wifi/forget` | `POST` | Removes one stored network from RAM and NVS and restarts the search. Credentials are never dropped by the device on its own | `{"slot":n}` (0–4) | `application/json` (`status`, `slot`, `ssid`, `nvsOk`) |
| `/api/time` | `POST` | Syncs system clock from browser | JSON body `{"timestamp":1700000000}` (integer epoch s; must fall in 2020–2100) | `application/json` (`{"status":"ok"}` / `400` with reason when out of range) |
| `/api/odo` | `GET` | Reads odometer distance in km | None | `application/json` |
| `/api/odo` | `POST` | Sets odometer distance | `{"km": 123.45}` | `application/json` |
| `/api/trip/reset` | `POST` | Zeros the trip stats (same reset as the GPIO25 button); the odometer and session max speed are untouched | None | `application/json` |
| `/api/reboot` | `POST` | Triggers graceful device restart | None | `text/plain` |
| `/api/sleep` | `POST` | Triggers immediate deep sleep | None | `text/plain` |
| `/api/reset` | `POST` | Factory reset — clears the `cfg` namespace; WiFi credentials and the odometer survive | None | `text/plain` |
| `/api/ambient` | `GET` | Reads raw ambient light sensor value | None | `application/json` |
| `/api/sensors` | `GET` | Reads calibrated battery voltage (`v`) and coolant temperature (`t`) | None | `application/json` |
| `/api/fuel` | `GET` | Reads the fuel input: `raw` averaged ADC code, `liters`, `pct`, `ohm` sender resistance, `st` input state (0 = disabled, 1 = ok, 2 = open circuit, 3 = shorted) | None | `application/json` |
| `/api/live` | `GET` | Single 1 Hz snapshot for the Web UI's live readings: `ambient`, `odo` (km), `fuel_raw`, `fuel_ohm`, `fuel_st`, `volts`, `temp`. One response feeds all five cells, so they always show the same instant | None | `application/json` |
| `/api/snapshot` | `GET` | Full 1 Hz vehicle + GNSS snapshot for external consumers (the Android app's trip recorder): `ver`, `up` (uptime s), `spd`, `src` (0 = Hall, 1 = GPS, 2 = fused), `avg`, `max`, `trp_km`, `trp_l`, `ikml`, `akml`, `odo` (km, demo-aware), `fuel_l`, `fuel_pct`, `fuel_st`, `volts`, `temp`, `amb`, `sats`, `hdop`, `alt`, `lat`, `lon`, `fix`, `tmr_st`, `tmr_s`, `fps`, `heap`. `fix` is 1 only while the GNSS location is valid (`lat`/`lon` meaningful then); `hdop` and `alt` print `-1` when the fix carried neither. Read-only and allocation-free like `/api/live` | None | `application/json` |
| `/api/noisematrix` | `GET` | Noise-bench snapshot: `status` (`never` / `running` / `done`), completed runs, and per run / per channel `mean`, `sigma` and peak-to-peak in mV and ADC codes (`_mv` / `_lsb`) | None | `application/json` |
| `/api/noisematrix` | `POST` | Starts the four-run sensor noise bench (`idle`, `tft`, `bl10`, `bl90`); runs in the background for ~17 s, so poll the `GET`. Answers `409` while a job is running | None | `application/json` |
| `/api/ambient/cal-dark` | `POST` | Sets dark-reference ambient light value (auto-brightness floor) | None | `application/json` (`{"status":"ok"\|"saved-ram-only","value":N}` — `saved-ram-only` means the value is applied but the NVS write failed) |
| `/api/ambient/cal-bright` | `POST` | Sets bright-reference ambient light value (auto-brightness ceiling) | None | `application/json` (same shape as `cal-dark`) |
| `/api/ota` | `POST` | Firmware install over the LAN — version, size, image-header and one-writer gates always; no signature step on any path; an **older** image is accepted without a flag (see *LAN install (`POST /api/ota`)*) | `multipart/form-data`: `target_version`, `firmware` (file part); optional `total_bytes`, `force=1` (reflash the identical build). A `signature` part may still be sent: it is counted, ignored and logged | `application/json` |
| `/api/ota/check` | `GET` | Reports **install state** for whoever is pushing the image: `state` (`idle|staging|receiving|verifying|writing|done|error`), `percent` (`-1` when no `total_bytes` was declared), `bytes`, `bytes_total`, `quiet`, `quiet_silent_ms`, `screen`, `hold_to_restart_ms`, `error`, `last_target_version`, plus the unit's identity — `current_version` (the compiled-in build, which is what every gate compares against), `build_version`, `image_tag` (the `DPPVER=` marker this build carries inside its own image file), `previous_version`, `status`, `status_updated`. The pull-era fields `enabled`, `url`, `ca_bundle` and `ca_mode` are gone: this unit fetches nothing by itself. Answers normally even during a quiet window — it is on the allow-list | None | `application/json` |
| `/api/serial` | `GET` | Streams internal 4 KB ring buffer logs | None | `text/plain` |
| `/api/perf` | `GET` | Live telemetry (CPU, Heap, task stack headroom, FPS, WiFi, partitions), plus the web task's own timing: `web_serve_ms_last` / `web_serve_ms_max` (what one `handleClient()` pass costs) and `web_slow_iters` (loop iterations over 100 ms). Also reports `mac`: the base eFuse MAC (uppercase, colon-separated) - the stable device identity the companion app binds its vehicle card to, unchanged by Wi-Fi mode or DHCP | None | `application/json` |
| `/api/health` | `GET` | Health probe: heap, FPS, partition layout and the NVS entry budget (`nvs_bytes`, `nvs_entries_used` / `_available` / `_total`) | None | `application/json` |
| `/api/boot` | `GET` | Boot/reboot forensics (reset reason, storm, last-reboot tag, heap watermark). `reset_reason` covers the whole core enum — `POWERON`, `EXT`, `SW (clean restart)`, `PANIC (crash/abort)`, `INT_WDT`, `TASK_WDT`, `WDT (other)`, `DEEP_SLEEP_WAKE`, `BROWNOUT`, `SDIO`, `USB`, `JTAG`, `EFUSE_ERR`, `PWR_GLITCH`, `CPU_LOCKUP`, `UNKNOWN`; anything unmapped prints `RST_<n>` (issue #42) | None | `application/json` |

### Noise Bench

A bench instrument (master plan step 8) that answers "how steady are the sensor
readings, and what on the board makes them wobble?" It samples the four real
sensor inputs — `BAT_SNS`/GPIO35, `COOL_SNS`/GPIO36, `LDR_SNS`/GPIO34,
`FUEL_SNS`/GPIO32 — 4,000 times per channel at ~1 kS/s and reports mean,
standard deviation and peak-to-peak in millivolts and ADC code counts. The four
runs are normal running conditions only: `idle`, `tft` (full-frame repaint on
every display tick), `bl10` and `bl90` (backlight held at 10 % / 90 %).

The sensor task pauses its own ADC reads while a job runs (ADC1 has one
converter), so the dashboard keeps animating but its sensor values hold for the
~17 s duration. Nothing is written to NVS; the result is transient.

**Before you start:** power the board as it will run in the vehicle (12 V on J1,
real sensors on their connectors — the battery divider is on-board, the coolant
NTC, LDR and fuel sender plug into theirs). If no fuel sender is wired, fit a
resistor across `FUEL_SNS` to GND (100 Ω is a sane reference) so the pin is not
floating. Do not change settings or touch the power wiring during a job — a
brightness change or a connector wiggle is itself a disturbance.

**From the WebUI (no PC needed):** open the dashboard page from any browser on
the device's AP or LAN, expand **Sensors Tuning** and press **Run Noise Test**
in the Noise Bench card. The card shows progress and then the full table — per
input, the mean, the wobble (σ), the extra wobble against the quiet baseline
(green at the target, amber above it) and the worst jump. The result lives in
RAM, so it is gone after a reboot.

**From the API / serial (automation):** put the device on WiFi so it has an IP
address, start a job with `Invoke-RestMethod -Method Post -Uri
http://<ip>/api/noisematrix` (or `curl -X POST http://<ip>/api/noisematrix`),
then poll `Invoke-RestMethod http://<ip>/api/noisematrix` until `status` is
`done` — or watch the serial log on COM7 at 115200 baud: the job prints one
`NB <run> <channel>: …` line per channel per run, then `NB DONE`.

**Reading the numbers:** `sigma_mv` is the wobble (the number to compare
between runs); `pp_mv` is the worst single jump. The `_lsb` fields are the same
statistics in ADC code counts (1 count ≈ 3.3 V / 4095 ≈ 0.806 mV — this is the
"LSB" the sensor conversions use, not a calibrated eFuse value). `interval_ms`
reports the sampling period actually achieved.

**Pass target (sensor plan D3, pin-referred):** a run's wobble (`sigma`) should
add no more than 0.5 ADC counts ≈ 0.40 mV on any pin compared with `idle`. This
is a design target to establish the baseline, not a hard failure; record the
numbers before and after a board change (respin, new harness) and compare.

---

## NVS Configuration Parameter Reference

Dashboard++ keeps every configuration parameter as one row of a single table, `CFG_TABLE` in `src/config.cpp`: the C++ global, the JSON key, the NVS key, the default, the allowed band and the kind (`CK_INT` / `CK_UINT` / `CK_FLT` / `CK_BOOL` / `CK_STR` / `CK_SECRET`) all on one line. `processConfig()` walks that table in its three modes — boot load, JSON serialize (`GET /api/config`) and restore/save (`POST /api/config`) — across 197 parameters (192 regular + 5 WiFi secrets), plus the fuel-calibration table kept beside it.

### Numeric Range Validation (issue #21)

Every numeric parameter carries an explicit **known-good band** in its `CFG_TABLE` row in `src/config.cpp` (`lo`/`hi` for `CK_INT` / `CK_UINT`, `flo`/`fhi` for `CK_FLT`) — that table is the single source of truth. The band is enforced on **all three write paths** (boot load, `POST /api/config`, and config restore): an out-of-range value is **clamped to the nearest end of the band, logged by name, and the clamped value is what gets written to NVS** — a bad value never reaches the running system, and a restore is never rejected outright because one field is off.

- **Non-finite floats** (`nan`, `inf`) fall back to the parameter's default rather than poisoning a calculation.
- **Cross-field rules** are repaired after the per-field clamps, in one place (`sanitizeConfigPairs()`): `TEMP_BAR_MIN < TEMP_BAR_MAX`, `TEMP_BAR_MIN <= TEMP_WARN_LOW <= TEMP_WARN_YEL <= TEMP_WARN_RED <= TEMP_BAR_MAX` (the three temp color fade points, repaired cold→hot so a band can never flip direction), `FUEL_WARN_RED <= FUEL_WARN_YEL` (fuel is mirrored — it turns red *below* its marker), `LIGHT_SENSOR_DARK_VAL < LIGHT_SENSOR_BRIGHT_VAL`, `MIN_SATELLITES <= OPTIMAL_SATELLITES`, `CPU_THROTTLE_TEMP_WARN <= CPU_THROTTLE_TEMP_CRIT`.
- **Enumerated parameters** are snapped to the nearest legal step: `GPS_BAUD` to a standard u-blox rate (1200…921600), `MANUAL_CPU_FREQ` to 80 / 160 / 240 MHz. `DISPLAY_ROTATION` is masked to 0–3, `WHEEL_CIRCUMFERENCE_MM` has always been floored at 1 (it is a divisor).
- **Fuel calibration table** (`fuelCalOhms`) cells are clamped to the sender band 0–100000 Ω on load and on restore. The table is in **ohms** since issue #18 (it used to be raw ADC codes under the name `touchTable`); old `touchTable` values in a backup are ignored rather than re-injected as ohms. The table is also required to be **monotonic in one direction** (the direction its first and last entries already imply): out-of-order points are sorted by `repairFuelTable()` on boot load and on save, written back to NVS, and named in the log, because a gap in the ramp would otherwise freeze the needle (issue #19). The gauge walk in `src/sensors.cpp` carries a second layer — a reading that matches no segment parks on the nearer end and logs once every 5 s instead of leaving the last value in place.
- The **WebUI mirrors the same bands** so a bad entry is caught before it is posted: numeric inputs get `min`/`max` from a `FIRMWARE_LIMITS` table generated out of `config.cpp` (`python scripts/make_webui_limits.py` regenerates it after any band change), an out-of-range entry is corrected in the box and listed in the save message, and an emptied numeric box falls back to its default instead of posting a blank (which the device used to read as `0`).

Bands are also checked offline by `python scripts/verify_config_ranges.py`: every numeric parameter must have a band, no shipped default may fall outside its own band, and the cross-field rules must hold for the factory values.

### NVS Access, Locking & Write Errors (issue #32)

ESP-IDF's NVS layer has its own internal locking, so a torn write is unlikely — what is *not* protected is the session. Two tasks opening and closing the same namespace independently can still collide: one task's `end()` closes the handle the other is still using, which comes back as `ESP_ERR_NVS_*` from `putInt()`/`putString()` and shows up as a setting that quietly reverted after a reboot. The old code took `prefsMux` at some call sites and not at others, so the protection depended on which file the code happened to live in.

- Every namespace open now goes through **`NvsSession`** (`src/dashboard.h`): an RAII wrapper that holds `prefsMux` for the whole `begin()`/`end()` pair, logs when a namespace cannot be opened, and closes on scope exit so an early return cannot leak the handle. It skips the lock while `prefsMux` is still `NULL` (early boot, single-threaded). The long-lived `preferences` object for the `dashboard` namespace keeps its explicit `prefsMux` pairs.
- **Write results are checked.** `nvsWriteFailed(key, esp_err_t)` logs the failing key with `esp_err_to_name()`; the table-driven save counts them (`cfgApply()` bumps `cfgNvsWriteErrors` for every row that fails) and a save ends with `Config save: N parameter(s) failed to reach NVS … they will revert on reboot` instead of pretending nothing happened. The same check covers the fuel-table writes, the factory-reset credential restore, the bootinfo writes and the ambient calibrations.
- **A failed read is not a default.** Where an unreadable NVS would previously have produced "no value" and triggered a factory seed, the seed is now skipped with a log line — a flash that cannot be read must never be answered by overwriting it.
- **Factory defaults are the table.** On first boot (`CFG_VER` missing or below 5) the seed writes each `CFG_TABLE` default straight into NVS and RAM (`cfgSeedDefaults()`, one `NvsSession` for the whole pass) — there is no second copy of the defaults in flash and no `JsonDocument` to build one. The WiFi credentials are deliberately not seeded, so a lost `CFG_VER` stamp can never strand a unit without a network, and the fuel ramp is rebuilt from the seeded `FUEL_OHM_EMPTY`/`FUEL_OHM_FULL` only when the stored table is not already the factory ramp.
- `prefsMux` is a plain (non-recursive) mutex: nothing inside a locked NVS region may open NVS itself.

### Key Configuration Categories

#### System & Performance
- `TARGET_FPS` (default=60): Desired display refresh rate, **5–120 FPS** (band-checked on load and in the Web UI). It sets the derived `DISPLAY_REFRESH_MS` frame budget (120 → 8 ms, 60 → 16 ms, 5 → 200 ms); values above what the SPI panel can carry simply drop the FPS counter rather than saturating the display core (issue #36).
- `SPI_BUS_SPEED` (default=60000000): SPI bus frequency in Hz. Accepted range **1000000–80000000** (1–80 MHz; WebUI shows MHz). Out-of-range values are clamped on load/save — a `0` or a negative (wrapped) value would otherwise feed LovyanGFX a degenerate clock divider and blank the panel. The read clock is derived as `SPI_BUS_SPEED × 8/5`, computed in 64-bit and clamped to the same band.
- `ENABLE_DYNAMIC_CPU` (default=false): Toggles automatic CPU frequency scaling (hysteresis-based).
- `MANUAL_CPU_FREQ` (default=240): Fixed CPU clock frequency (80, 160, or 240 MHz) used when `ENABLE_DYNAMIC_CPU` is off. The value is snapped to the nearest legal step, and every `setCpuFrequencyMhz()` call now checks its result — a refused switch logs `CPU: refused to switch to …MHz` instead of claiming a frequency the chip never switched to (issue #34).
- `ENABLE_CPU_THROTTLE` (default=true): Enables thermal frequency capping.
- `CPU_THROTTLE_TEMP_WARN` (default=60): Warning temperature threshold in °C.
- `CPU_THROTTLE_TEMP_CRIT` (default=70): Critical temperature threshold in °C.

#### Web UI
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
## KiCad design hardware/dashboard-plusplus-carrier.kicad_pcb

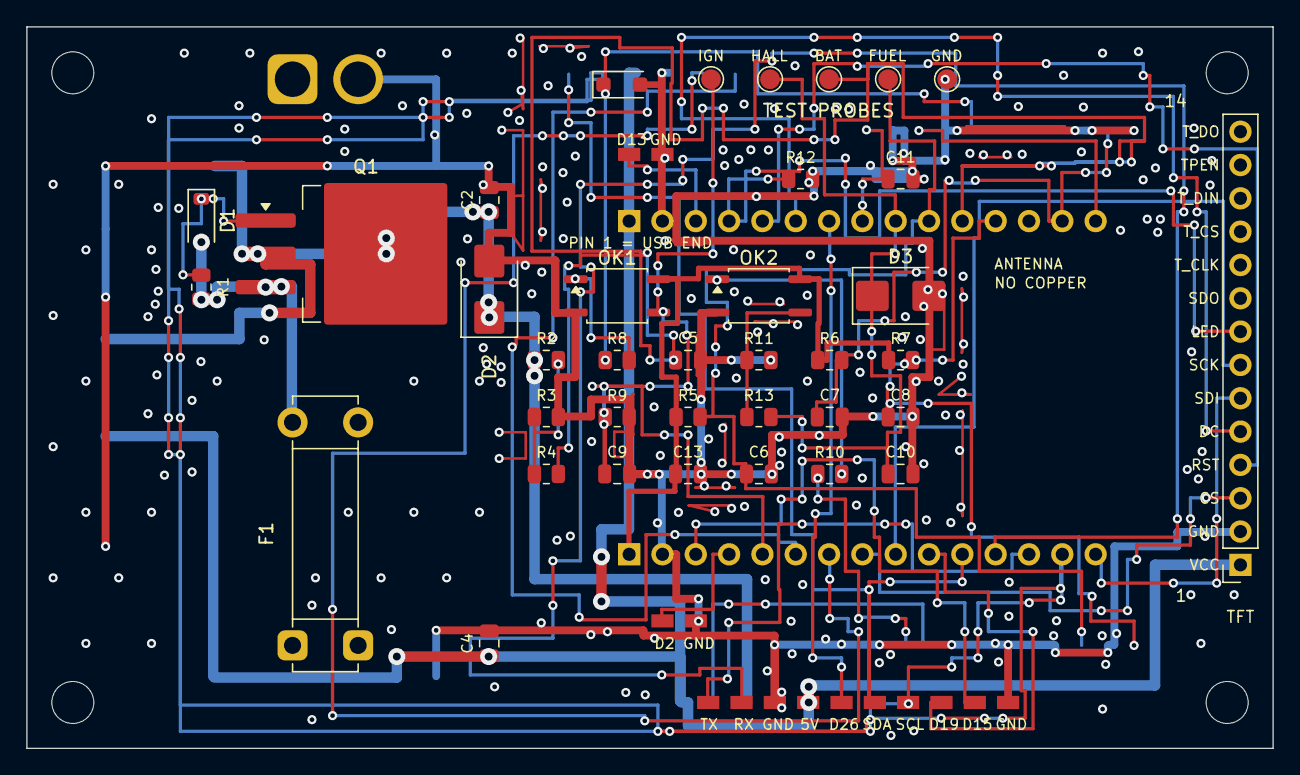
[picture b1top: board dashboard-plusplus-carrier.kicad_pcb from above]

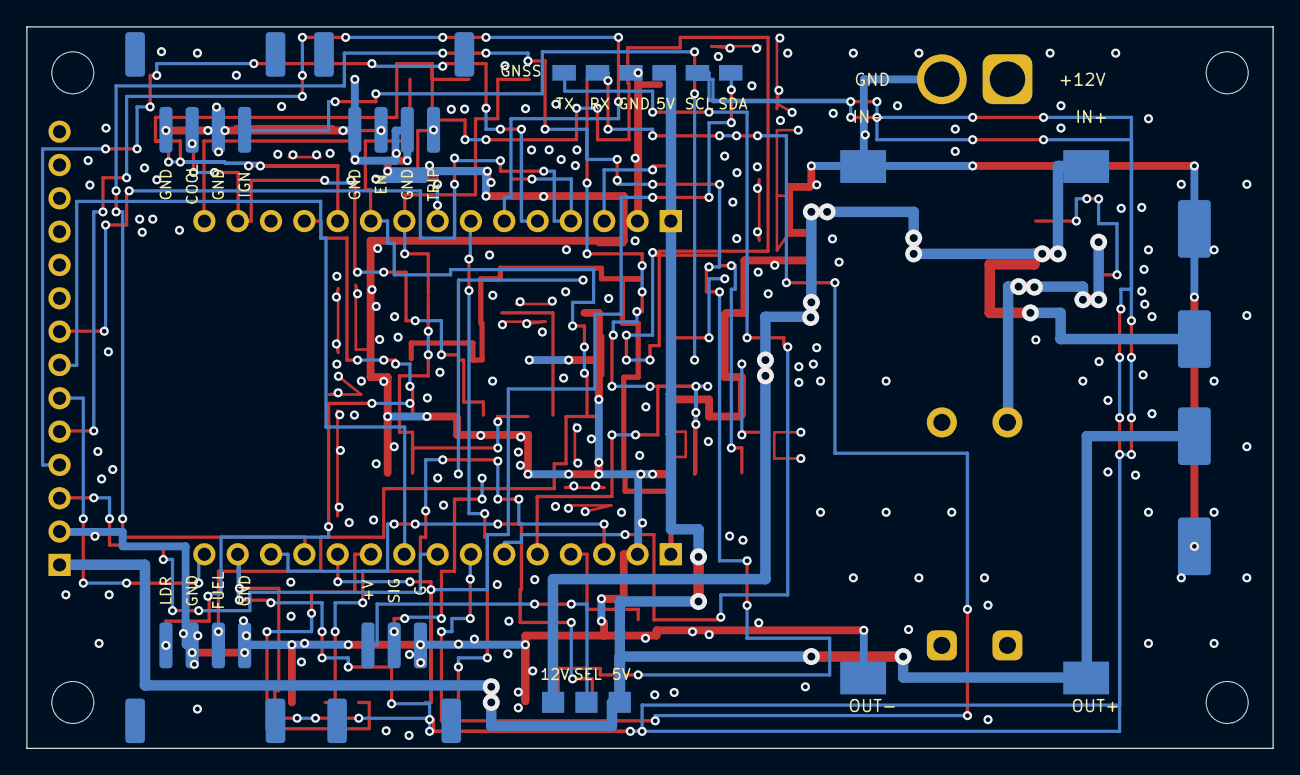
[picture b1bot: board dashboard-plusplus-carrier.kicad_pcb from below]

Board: 4 copper layers, 95.0 x 55.0 mm, 57 parts (12 on the bottom side), 39 nets.

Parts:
C1: 220u/50V; CP_Elec_10x12.5
C2, C4, C5, C6, C7, C8, C9, C10, C11, C13: 100n; C_0805_2012Metric
C3: 470u/35V; CP_Elec_10x12.5
D1: BZT52C15V; D_SOD-123
D2: P6SMB33A; D_SMB
D3: P6SMB6V2A; D_SMB
D4: SMF4L33A; D_SOD-123F
F1: 5x20 2A; Fuseholder_Clip-5x20mm_Littelfuse_521_Lateral_P17.00x5.00mm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
H1, H2, H3, H4: MOUNT
J1: XT30U-M; AMASS_XT30U-M_1x02_P5.0mm_Vertical
J3: TFT-ILI9488; PinSocket_1x14_P2.54mm_Vertical
J6: LDR + FUEL; JST_PH_S4B-PH-SM4-TB_1x04-1MP_P2.00mm_Horizontal
J8: GPS_PADS
J9: HALL; JST_PH_S3B-PH-SM4-TB_1x03-1MP_P2.00mm_Horizontal
J10a: ESP32-DEVKIT-A; PinSocket_1x15_P2.54mm_Vertical
J10b: ESP32-DEVKIT-B; PinSocket_1x15_P2.54mm_Vertical
J13: DEBUG
J14: TRIP + EN; JST_PH_S4B-PH-SM4-TB_1x04-1MP_P2.00mm_Horizontal
J15: SPARE
J16: SPARE N; SPARE_N
J17: IGN + COOLANT; JST_PH_S4B-PH-SM4-TB_1x04-1MP_P2.00mm_Horizontal
J18: SPARE S; SPARE_S
JP1: JP1_PADS_3
OK1, OK2: EL357N-B; SO-4_4.4x3.9mm_P2.54mm
Q1: IRFR9540N; TO-263-3_TabPin2
R1, R3, R6, R7, R9, R11, R12: 10k; R_0805_2012Metric
R2: 47k; R_0805_2012Metric
R4, R8, R10, R13: 1k; R_0805_2012Metric
R5: 220R; R_0805_2012Metric
TP1: IGN_SENSE; TestPoint_Pad_D1.5mm
TP2: HALL; TestPoint_Pad_D1.5mm
TP3: BAT_SNS; TestPoint_Pad_D1.5mm
TP4: FUEL_SNS; TestPoint_Pad_D1.5mm
TP5: GND; TestPoint_Pad_D1.5mm
U4: DPP_DCDC_MODULE

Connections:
BAT_DIV: R2.2, R3.1, R4.1
BAT_SNS: C5.1, J10a.11, R4.2, TP3.1
COOL_SNS: C7.1, J10a.14, J17.3, R6.2
DBG_RX: J10b.12, J13.2
DBG_TX: J10b.13, J13.1
DC_12: C1.1, C2.1, D2.1, JP1.3, Q1.2, R2.1, U4.1
DC_F: D1.2, F1.2, Q1.3, R1.2
DC_IN: F1.1, J1.1
EN: J10a.15, J14.3
FUEL_SNS: C6.1, J6.3, J10a.10, R5.2, TP4.1
GND: C1.2, C2.2, C3.2, C4.2, C5.2, C6.2, C7.2, C8.2, C9.2, C10.2, C11.2, C13.2, D2.2, D3.2, D4.2, J1.2, J3.2, J6.2, J6.4, J8.4, J9.3, J10a.2, J10b.2, J13.3, J14.2, J14.4, J15.6, J16.2, J17.2, J17.4, J18.2, OK1.2, OK2.2, R3.2, R9.2, R11.2, R12.2, TP5.1, U4.2, U4.4
GPS_RX: J8.6, J10b.6
GPS_TX: J8.5, J10b.7
HALL: C10.1, D3.1, J10a.9, R13.2, TP2.1
HALL_LED: OK2.1, R10.2
HALL_OUT: OK2.3, R11.1, R13.1
HALL_SIG: J9.2, R10.1
HALL_VCC: J9.1, JP1.2
IGN_12: D4.1, J17.1, R8.1
IGN_LED: OK1.1, R8.2
IGN_SENSE: C9.1, J10b.5, OK1.3, R9.1, TP1.1
LDR_SNS: C8.1, J6.1, J10a.12, R7.2
MOS_G: D1.1, Q1.1, R1.1
SPARE_D2: J10b.4, J18.1
SPARE_D13: J10a.3, J16.1
SPARE_D15: J10b.3, J15.5
SPARE_D19: J10b.10, J15.4
SPARE_D21: J8.1, J10b.11, J15.2
SPARE_D22: J8.2, J10b.14, J15.3
SPARE_D26: J10a.7, J15.1
TFT_BL: J3.8, J10a.4, R12.1
TFT_CS: J3.3, J10b.8
TFT_DC: J3.5, J10a.6
TFT_MOSI: J3.6, J10b.15
TFT_RST: J3.4, J10a.5
TFT_SCK: J3.7, J10b.9
TRIP_BTN: C11.1, J10a.8, J14.1
V3V3: C13.1, J10b.1, OK1.4, OK2.4, R5.1, R6.1, R7.1
V5: C3.1, C4.1, J3.1, J8.3, J10a.1, J13.4, JP1.1, U4.3

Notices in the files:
README.md:
Designed and engineered by **alefinot**.
- Built using [LovyanGFX](https://github.com/lovyan03/LovyanGFX) for high-speed SPI display driving.
- GPS parsing powered by [TinyGPSPlus](https://github.com/mikalhart/TinyGPSPlus).
- Configuration engine powered by [ArduinoJson](https://arduinojson.org/).
Copyright © alefinot — Dashboard++ for ESP32
License: MIT
